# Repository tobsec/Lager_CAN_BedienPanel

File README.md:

Lager_CAN_BedienPanel
=====================

3teiliges Bedienpanel

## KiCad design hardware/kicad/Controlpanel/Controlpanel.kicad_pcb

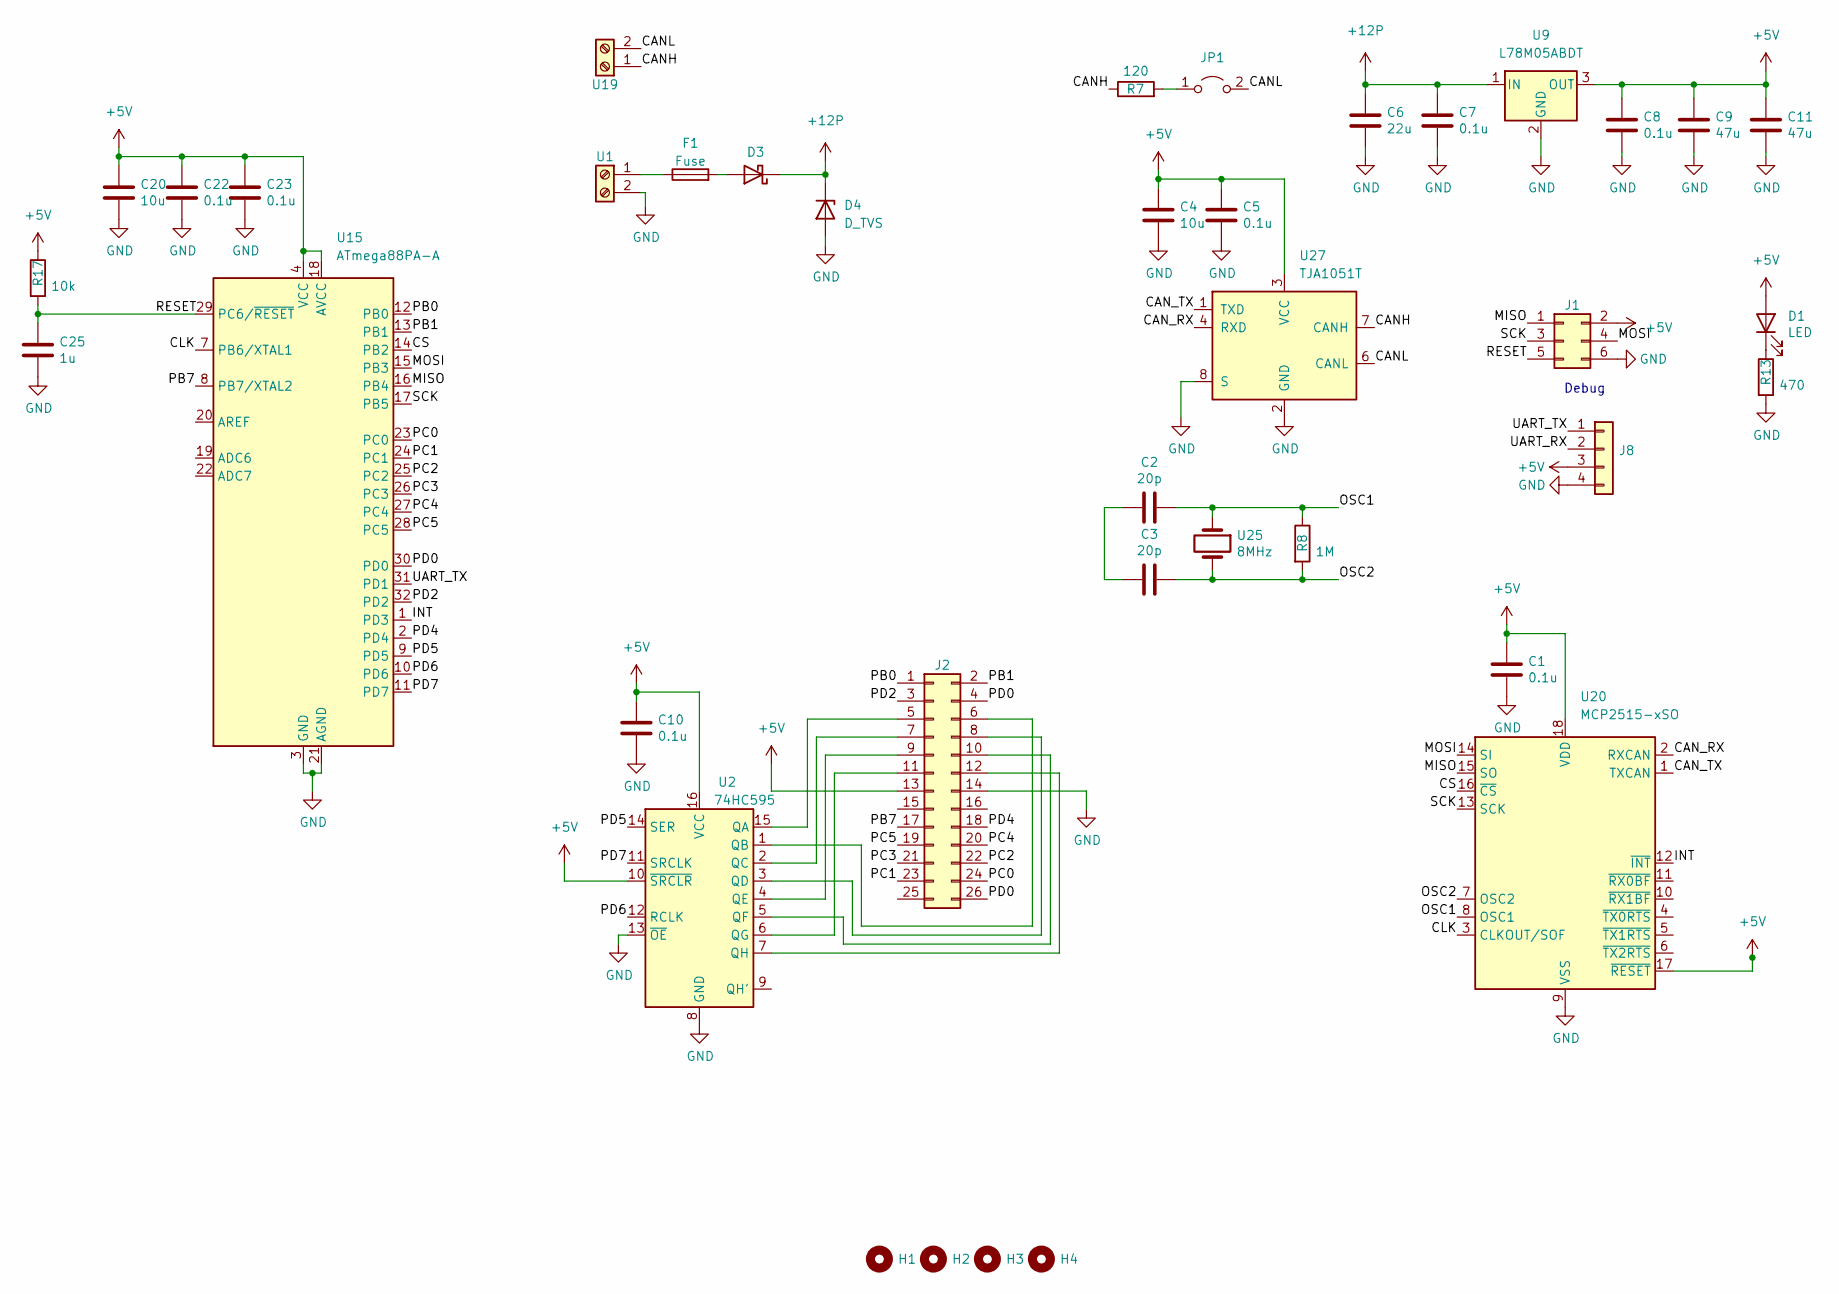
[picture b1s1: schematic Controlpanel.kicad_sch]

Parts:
C1, C5, C7, C8, C10, C22, C23: 0.1u; C_0805_2012Metric; MPN C49678
C2, C3: 20p; C_0805_2012Metric; MPN C1798
C4, C20: 10u; C_0805_2012Metric; MPN C15850
C6: 22u; C_1206_3216Metric; MPN C12891
C9, C11: 47u; C_1206_3216Metric; MPN C96123
C25: 1u; C_0805_2012Metric; MPN C28323
D1: LED; LED_0603_1608Metric; MPN C2286
D3: 738-5052; D_SMA; MPN C14996
D4: D_TVS; D_SMA; MPN C19077535
F1: Fuse; Fuse_1812_4532Metric
H1, H2, H3, H4: MountingHole; MountingHole_4.3mm_M4
J1: Conn_02x03_Odd_Even; PinHeader_2x03_P2.54mm_Vertical
J2: Conn_02x03_Odd_Even; PinHeader_2x13_P2.54mm_Vertical
J8: Conn_01x04; PinHeader_1x04_P2.54mm_Vertical
JP1: Jumper_2_Open; PinHeader_1x02_P2.54mm_Vertical
R7: 120; R_0805_2012Metric; MPN C17437
R8: 1M; R_0805_2012Metric; MPN C17514
R13: 470; R_0805_2012Metric; MPN C17710
R17: 10k; R_0805_2012Metric
U1, U19: Screw_Terminal_01x02; TerminalBlock_Altech_AK300-2_P5.00mm
U2: 74HC595; SO-16_3.9x9.9mm_P1.27mm
U9: L78M05ABDT; TO-252-2; MPN C58069
U15: ATmega88PA-A; TQFP-32_7x7mm_P0.8mm; MPN C16190
U20: MCP2515-xSO; SOIC-18W_7.5x11.6mm_P1.27mm; MPN C12368
U25: 8MHz; Crystal_HC49-U_Vertical
U27: TJA1051T; SOIC-8_3.9x4.9mm_P1.27mm; MPN C6952

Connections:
+5V: C1.1, C4.2, C5.1, C8.1, C9.2, C10.1, C11.2, C20.2, C22.1, C23.1, D1.2 (A), J1.2, J2.13, J8.3, R17.1, U2.10 (~SRCLR), U2.16 (VCC), U9.3 (OUT), U15.4 (VCC), U15.6 (VCC), U15.18 (AVCC), U20.17 (~RESET), U20.18 (VDD), U27.3 (VCC)
+12P: C6.2, C7.1, D3.1 (K), D4.1 (K), U9.1 (IN)
/CANH: R7.1, U19.1, U27.7 (CANH)
/CANL: JP1.2 (B), U19.2, U27.6 (CANL)
/CAN_RX: U20.2 (RXCAN), U27.4 (RXD)
/CAN_TX: U20.1 (TXCAN), U27.1 (TXD)
/CLK: U15.7 (PB6/XTAL1), U20.3 (CLKOUT/SOF)
/CS: U15.14 (PB2), U20.16 (~CS)
/INT: U15.1 (PD3), U20.12 (~INT)
/MISO: J1.1, U15.16 (PB4), U20.15 (SO)
/MOSI: J1.4, U15.15 (PB3), U20.14 (SI)
/OSC1: C2.1, R8.1, U20.8 (OSC1), U25.1
/OSC2: C3.1, R8.2, U20.7 (OSC2), U25.2
/PB0: J2.1, U15.12 (PB0)
/PB1: J2.2, U15.13 (PB1)
/PB7: J2.17, U15.8 (PB7/XTAL2)
/PC0: J2.24, U15.23 (PC0)
/PC1: J2.23, U15.24 (PC1)
/PC2: J2.22, U15.25 (PC2)
/PC3: J2.21, U15.26 (PC3)
/PC4: J2.20, U15.27 (PC4)
/PC5: J2.19, U15.28 (PC5)
/PD0: J2.4, J2.26, U15.30 (PD0)
/PD2: J2.3, U15.32 (PD2)
/PD4: J2.18, U15.2 (PD4)
/PD5: U2.14 (SER), U15.9 (PD5)
/PD6: U2.12 (RCLK), U15.10 (PD6)
/PD7: U2.11 (SRCLK), U15.11 (PD7)
/RESET: C25.1, J1.5, R17.2, U15.29 (PC6/~RESET)
/SCK: J1.3, U15.17 (PB5), U20.13 (SCK)
/UART_RX: J8.2
/UART_TX: J8.1, U15.31 (PD1)
GND: C1.2, C4.1, C5.2, C6.1, C7.2, C8.2, C9.1, C10.2, C11.1, C20.1, C22.2, C23.2, C25.2, D4.2 (A), J1.6, J2.14, J8.4, R13.2, U1.2, U2.8 (GND), U2.13 (~OE), U9.2 (GND), U15.3 (GND), U15.5 (GND), U15.21 (AGND), U20.9 (VSS), U27.2 (GND), U27.8 (S)
unnamed: C2.2, C3.2
unnamed: D1.1 (K), R13.1
unnamed: D3.2 (A), F1.2
unnamed: J2.5, U2.15 (QA)
unnamed: J2.6, U2.1 (QB)
unnamed: J2.7, U2.2 (QC)
unnamed: J2.8, U2.3 (QD)
unnamed: J2.9, U2.4 (QE)
unnamed: J2.10, U2.5 (QF)
unnamed: J2.11, U2.6 (QG)
unnamed: J2.12, U2.7 (QH)
unnamed: JP1.1 (A), R7.2
unnamed: F1.1, U1.1

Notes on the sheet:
Debug

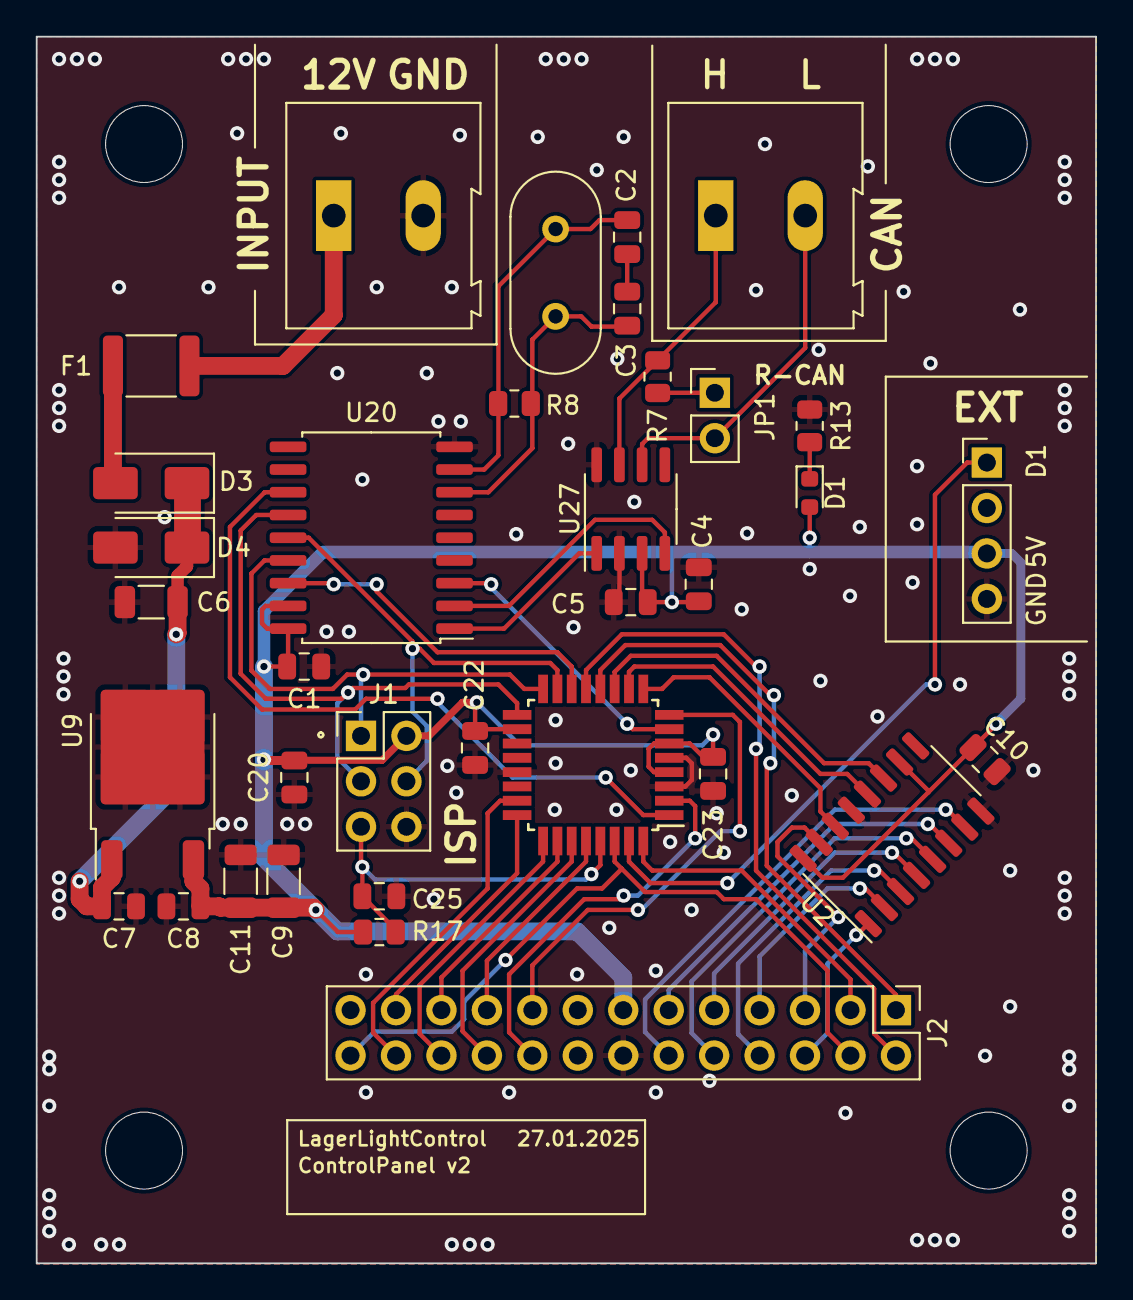
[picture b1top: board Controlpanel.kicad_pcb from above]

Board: 2 copper layers, 59.2 x 68.5 mm, 39 parts (0 on the bottom side), 45 nets.

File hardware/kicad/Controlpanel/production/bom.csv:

Designator,Footprint,Quantity,Value,LCSC Part #
"C1, C10, C22, C23, C5, C8",0805,6,0.1u,C49678
"C11, C9",1206,2,47u,C96123
"C2, C3",0805,2,20p,C1798
"C20, C4",0805,2,10u,C15850
C25,0805,1,1u,C28323
C6,1206,1,22u,C12891
C7,0805,1,0.1u,
D1,0603,1,LED,C2286
D3,D_SMA,1,738-5052,C14996
D4,D_SMA,1,D_TVS,C19077535
F1,1812,1,Fuse,
J2,PinHeader_2x13_P2.54mm_Vertical,1,Conn_02x03_Odd_Even,
R13,0805,1,470,C17710
R17,0805,1,10k,
R7,0805,1,120,C17437
R8,0805,1,1M,C17514
U2,SO-16_3.9x9.9mm_P1.27mm,1,74HC595,
U20,SOIC-18W_7.5x11.6mm_P1.27mm,1,MCP2515-xSO,C12368
U25,Crystal_HC49-U_Vertical,1,8MHz,
U27,SOIC-8_3.9x4.9mm_P1.27mm,1,TJA1051T,C6952
U9,TO-252-2,1,L78M05ABDT,C58069

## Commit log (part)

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2014-09-08 Commit des aktuellen Standes
2025-01-28 Convert to PlatformIO
2025-01-28 Add Eeagle PCB (old)
2025-01-28 Add KiCad PCB - as ordered
2025-01-28 add CAN requested reset for BL, LagerLight protocol V2, prepare CAN flashing
2025-01-28 Rework platformio for CAN flashing, add flashing batchs
2025-01-29 Refactored CAN functionality into a separate component and cleaned up indentation.
2025-02-15 Comments, adapt for the control panel PCB
